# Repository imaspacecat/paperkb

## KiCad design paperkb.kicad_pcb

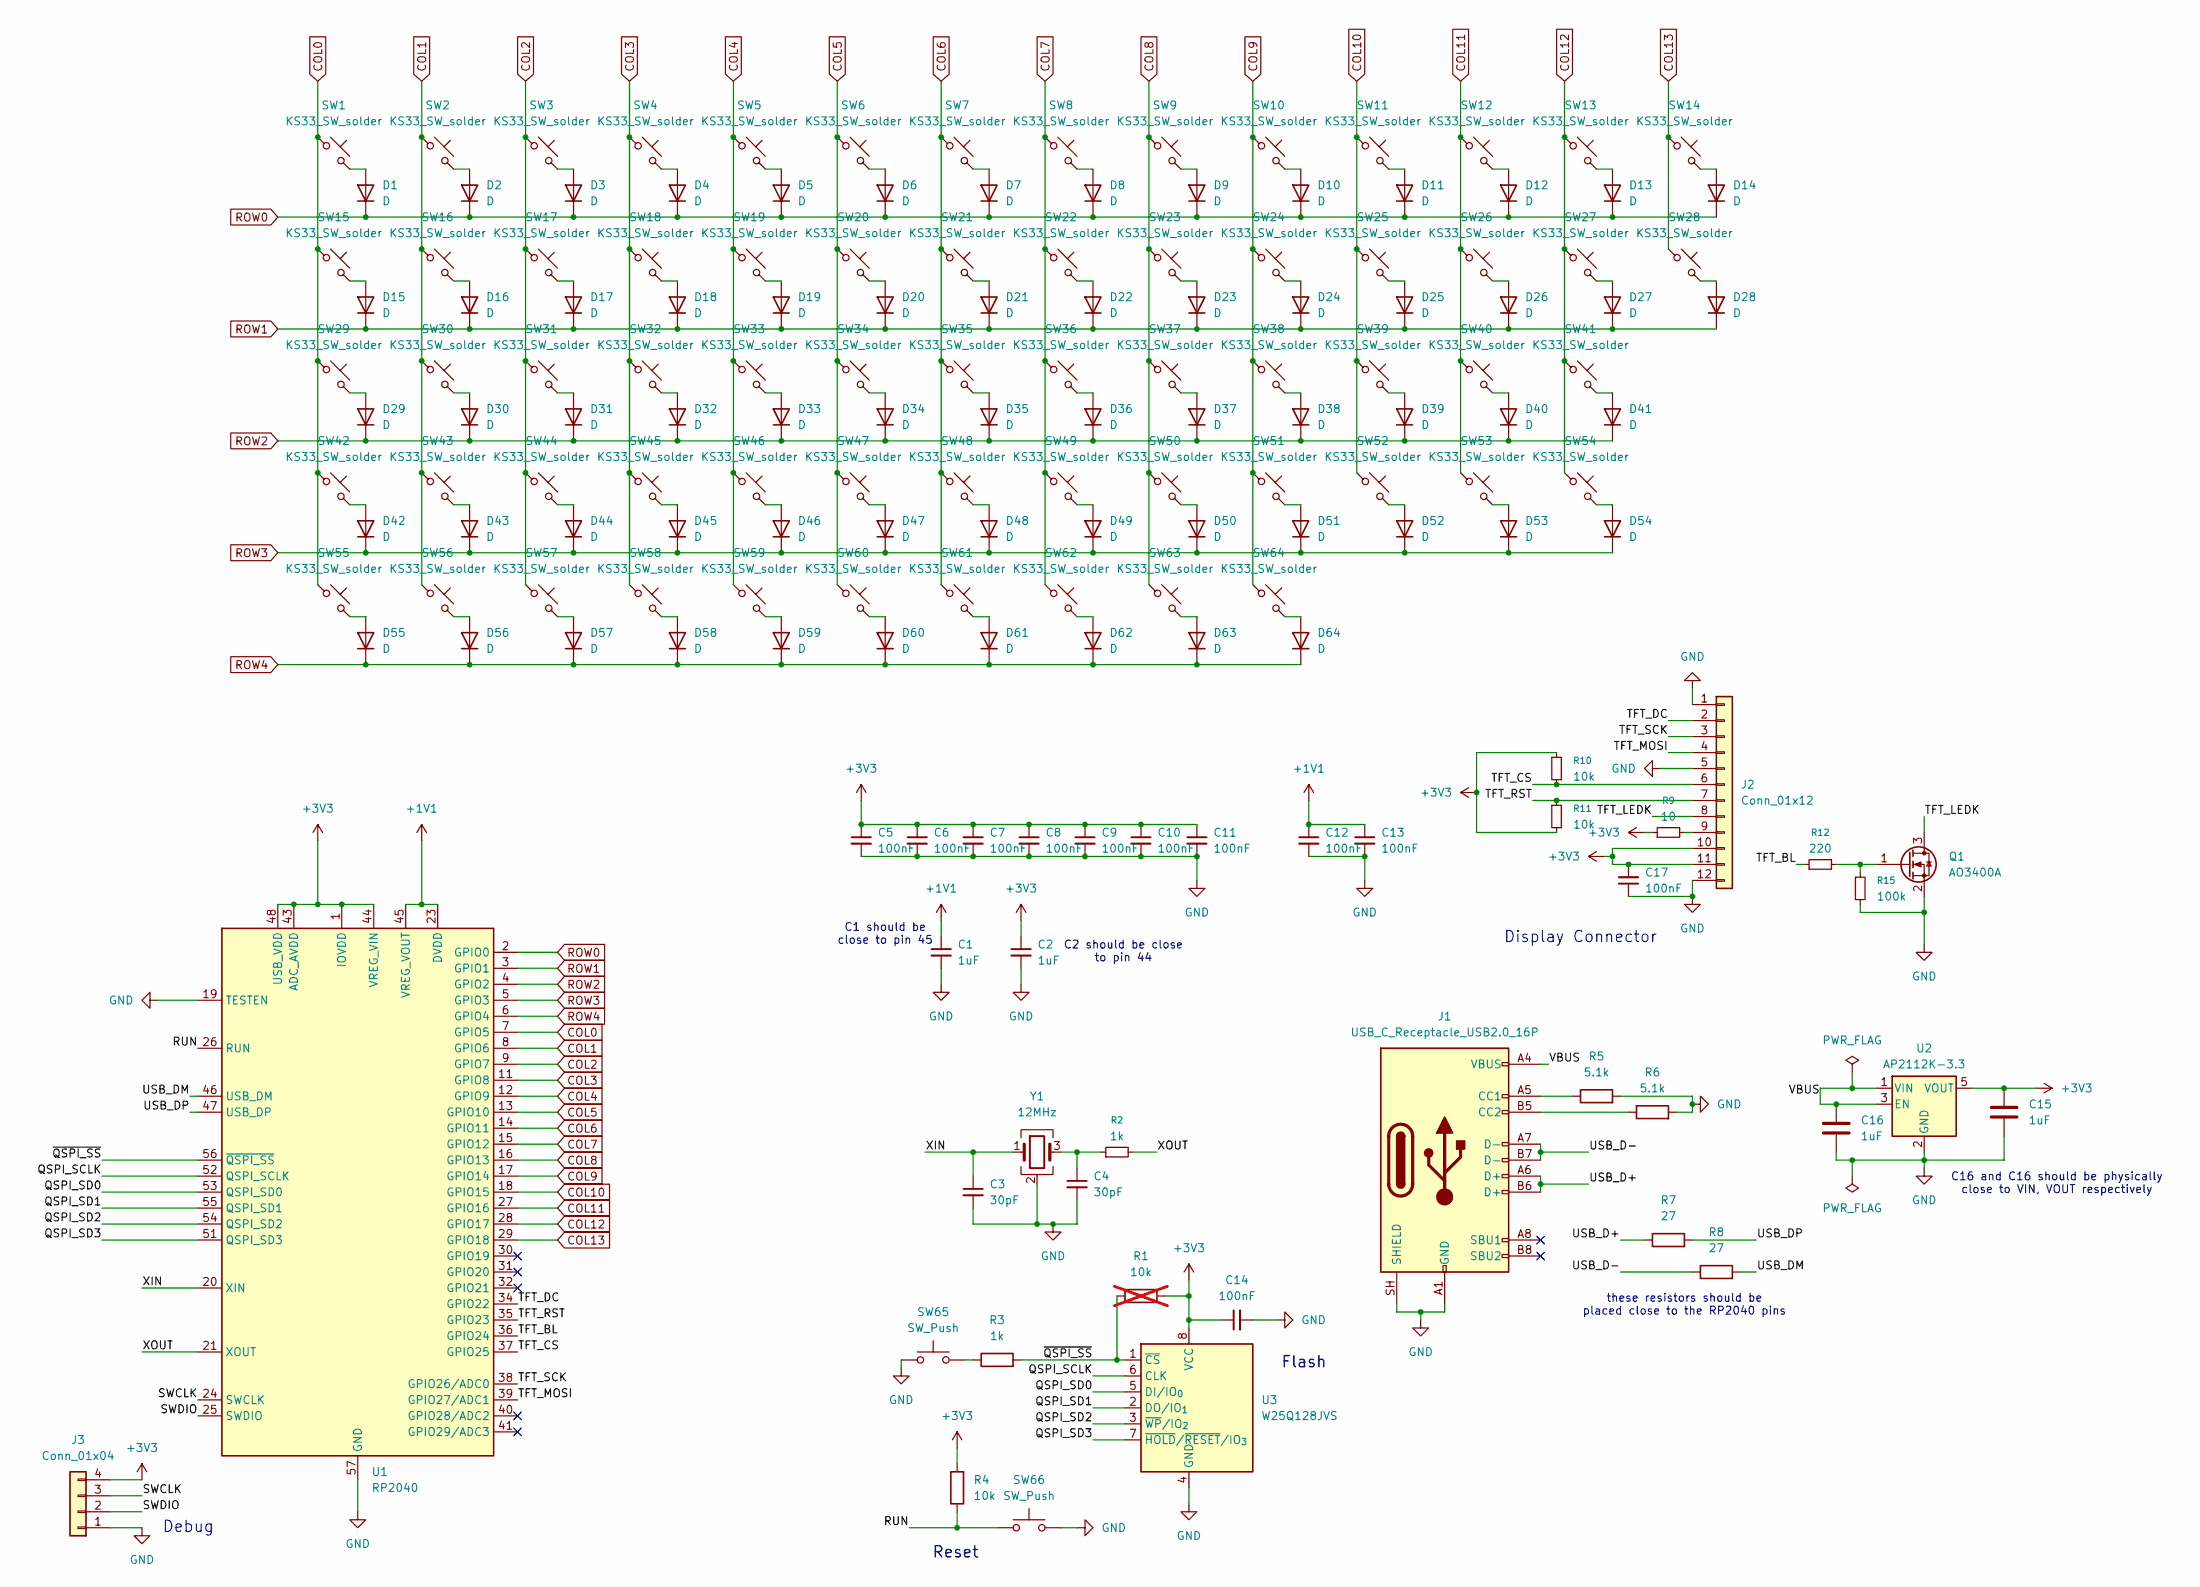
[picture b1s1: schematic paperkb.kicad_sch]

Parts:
C1, C2, C15, C16: 1uF; C_0603_1608Metric
C3, C4: 30pF; C_0603_1608Metric
C5, C6, C7, C8, C9, C10, C11, C12, C13, C14, C17: 100nF; C_0603_1608Metric
D1, D2, D3, D4, D5, D6, D7, D8, D9, D10, D11, D12, D13, D14, D15, D16, D17, D18, D19, D20, D21, D22, D23, D24, D25, D26, D27, D28, D29, D30, D31, D32, D33, D34, D35, D36, D37, D38, D39, D40, D41, D42, D43, D44, D45, D46, D47, D48, D49, D50, D51, D52, D53, D54, D55, D56, D57, D58, D59, D60, D61, D62, D63, D64: D; D_SOD-123
J1: USB_C_Receptacle_USB2.0_16P; USB_C_Receptacle_HRO_TYPE-C-31-M-12
J2: Conn_01x12; FPC-SMD_AFC01-S12FCA-00
J3: Conn_01x04; PinHeader_1x04_P2.54mm_Vertical
Q1: AO3400A; SOT-23
R1: 10k; R_0603_1608Metric; not fitted
R2, R3: 1k; R_0603_1608Metric
R4, R10, R11: 10k; R_0603_1608Metric
R5, R6: 5.1k; R_0603_1608Metric
R7, R8: 27; R_0603_1608Metric
R9: 10; R_0603_1608Metric
R12: 220; R_0603_1608Metric
R15: 100k; R_0603_1608Metric
SW1, SW2, SW3, SW4, SW5, SW6, SW7, SW8, SW9, SW10, SW11, SW12, SW13, SW14, SW15, SW16, SW17, SW18, SW19, SW20, SW21, SW22, SW23, SW24, SW25, SW26, SW27, SW28, SW29, SW30, SW31, SW32, SW33, SW34, SW35, SW36, SW37, SW38, SW39, SW40, SW41, SW42, SW43, SW44, SW45, SW46, SW47, SW48, SW49, SW50, SW51, SW52, SW53, SW54, SW55, SW56, SW57, SW58, SW59, SW60, SW61, SW62, SW63, SW64: KS33_SW_solder; SW_KS33_1u
SW65, SW66: SW_Push; SW_Push_1P1T_XKB_TS-1187A
U1: RP2040; QFN-56-1EP_7x7mm_P0.4mm_EP3.2x3.2mm
U2: AP2112K-3.3; SOT-23-5
U3: W25Q128JVS; SOIC-8_5.3x5.3mm_P1.27mm
Y1: 12MHz; Crystal_SMD_3225-4Pin_3.2x2.5mm

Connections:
+1V1: C1.1, C12.1, C13.1, U1.23 (DVDD), U1.45 (VREG_VOUT), U1.50 (DVDD)
+3V3: C2.1, C5.1, C6.1, C7.1, C8.1, C9.1, C10.1, C11.1, C14.1, C15.2, C17.2, J2.10, J2.11, J3.4, R1.2, R4.2, R9.1, R10.1, R11.2, U1.1 (IOVDD), U1.10 (IOVDD), U1.22 (IOVDD), U1.33 (IOVDD), U1.42 (IOVDD), U1.43 (ADC_AVDD), U1.44 (VREG_VIN), U1.48 (USB_VDD), U1.49 (IOVDD), U2.5 (VOUT), U3.8 (VCC)
/QSPI_SCLK: U1.52 (QSPI_SCLK), U3.6 (CLK)
/QSPI_SD0: U1.53 (QSPI_SD0), U3.5 (DI/IO_{0})
/QSPI_SD1: U1.55 (QSPI_SD1), U3.2 (DO/IO_{1})
/QSPI_SD2: U1.54 (QSPI_SD2), U3.3 (~WP/IO_{2})
/QSPI_SD3: U1.51 (QSPI_SD3), U3.7 (~HOLD/~RESET/IO_{3})
/RUN: R4.1, SW66.1, U1.26 (RUN)
/SWCLK: J3.3, U1.24 (SWCLK)
/SWDIO: J3.2, U1.25 (SWDIO)
/TFT_BL: R12.1, U1.36 (GPIO24)
/TFT_CS: J2.6, R10.2, U1.37 (GPIO25)
/TFT_DC: J2.2, U1.34 (GPIO22)
/TFT_LEDK: J2.8, Q1.3 (D)
/TFT_MOSI: J2.4, U1.39 (GPIO27/ADC1)
/TFT_RST: J2.7, R11.1, U1.35 (GPIO23)
/TFT_SCK: J2.3, U1.38 (GPIO26/ADC0)
/USB_D+: J1.A6 (D+), J1.B6 (D+), R7.1
/USB_D-: J1.A7 (D-), J1.B7 (D-), R8.1
/USB_DM: R8.2, U1.46 (USB_DM)
/USB_DP: R7.2, U1.47 (USB_DP)
/VBUS: C16.1, J1.A4 (VBUS), J1.A9 (VBUS), J1.B4 (VBUS), J1.B9 (VBUS), U2.1 (VIN), U2.3 (EN)
/XIN: C3.1, U1.20 (XIN), Y1.1
/XOUT: R2.2, U1.21 (XOUT)
/~QSPI_SS: R1.1, R3.2, U1.56 (~QSPI_SS), U3.1 (~CS)
COL0: SW1.1, SW15.1, SW29.1, SW42.1, SW55.1, U1.7 (GPIO5)
COL1: SW2.1, SW16.1, SW30.1, SW43.1, SW56.1, U1.8 (GPIO6)
COL2: SW3.1, SW17.1, SW31.1, SW44.1, SW57.1, U1.9 (GPIO7)
COL3: SW4.1, SW18.1, SW32.1, SW45.1, SW58.1, U1.11 (GPIO8)
COL4: SW5.1, SW19.1, SW33.1, SW46.1, SW59.1, U1.12 (GPIO9)
COL5: SW6.1, SW20.1, SW34.1, SW47.1, SW60.1, U1.13 (GPIO10)
COL6: SW7.1, SW21.1, SW35.1, SW48.1, SW61.1, U1.14 (GPIO11)
COL7: SW8.1, SW22.1, SW36.1, SW49.1, SW62.1, U1.15 (GPIO12)
COL8: SW9.1, SW23.1, SW37.1, SW50.1, SW63.1, U1.16 (GPIO13)
COL9: SW10.1, SW24.1, SW38.1, SW51.1, SW64.1, U1.17 (GPIO14)
COL10: SW11.1, SW25.1, SW39.1, SW52.1, U1.18 (GPIO15)
COL11: SW12.1, SW26.1, SW40.1, SW53.1, U1.27 (GPIO16)
COL12: SW13.1, SW27.1, SW41.1, SW54.1, U1.28 (GPIO17)
COL13: SW14.1, SW28.1, U1.29 (GPIO18)
GND: C1.2, C2.2, C3.2, C4.2, C5.2, C6.2, C7.2, C8.2, C9.2, C10.2, C11.2, C12.2, C13.2, C14.2, C15.1, C16.2, C17.1, J1.A1 (GND), J1.A12 (GND), J1.B1 (GND), J1.B12 (GND), J1.SH (SHIELD), J2.1, J2.5, J2.12, J3.1, Q1.2 (S), R5.2, R6.2, R15.2, SW65.1, SW66.2, U1.19 (TESTEN), U1.57 (GND), U2.2 (GND), U3.4 (GND), Y1.2 (G), Y1.4 (G)
unnamed: C4.1, R2.1, Y1.3
unnamed: D1.2 (A), SW1.2
unnamed: D2.2 (A), SW2.2
unnamed: D3.2 (A), SW3.2
unnamed: D4.2 (A), SW4.2
unnamed: D5.2 (A), SW5.2
unnamed: D6.2 (A), SW6.2
unnamed: D7.2 (A), SW7.2
unnamed: D8.2 (A), SW8.2
unnamed: D9.2 (A), SW9.2
unnamed: D10.2 (A), SW10.2
unnamed: D11.2 (A), SW11.2
unnamed: D12.2 (A), SW12.2
unnamed: D13.2 (A), SW13.2
unnamed: D14.2 (A), SW14.2
unnamed: D15.2 (A), SW15.2
unnamed: D16.2 (A), SW16.2
unnamed: D17.2 (A), SW17.2
unnamed: D18.2 (A), SW18.2
unnamed: D19.2 (A), SW19.2
unnamed: D20.2 (A), SW20.2
unnamed: D21.2 (A), SW21.2
unnamed: D22.2 (A), SW22.2
unnamed: D23.2 (A), SW23.2
unnamed: D24.2 (A), SW24.2
unnamed: D25.2 (A), SW25.2
unnamed: D26.2 (A), SW26.2
unnamed: D27.2 (A), SW27.2
unnamed: D28.2 (A), SW28.2
unnamed: D29.2 (A), SW29.2
unnamed: D30.2 (A), SW30.2
unnamed: D31.2 (A), SW31.2
unnamed: D32.2 (A), SW32.2
unnamed: D33.2 (A), SW33.2
unnamed: D34.2 (A), SW34.2
unnamed: D35.2 (A), SW35.2
unnamed: D36.2 (A), SW36.2
unnamed: D37.2 (A), SW37.2
unnamed: D38.2 (A), SW38.2
unnamed: D39.2 (A), SW39.2
unnamed: D40.2 (A), SW40.2
unnamed: D41.2 (A), SW41.2
unnamed: D42.2 (A), SW42.2
unnamed: D43.2 (A), SW43.2
unnamed: D44.2 (A), SW44.2
unnamed: D45.2 (A), SW45.2
unnamed: D46.2 (A), SW46.2
unnamed: D47.2 (A), SW47.2
unnamed: D48.2 (A), SW48.2
unnamed: D49.2 (A), SW49.2
unnamed: D50.2 (A), SW50.2
unnamed: D51.2 (A), SW51.2
unnamed: D52.2 (A), SW52.2
unnamed: D53.2 (A), SW53.2
unnamed: D54.2 (A), SW54.2
unnamed: D55.2 (A), SW55.2
unnamed: D56.2 (A), SW56.2
unnamed: D57.2 (A), SW57.2
unnamed: D58.2 (A), SW58.2
unnamed: D59.2 (A), SW59.2
unnamed: D60.2 (A), SW60.2
unnamed: D61.2 (A), SW61.2
unnamed: D62.2 (A), SW62.2
unnamed: D63.2 (A), SW63.2
unnamed: D64.2 (A), SW64.2
unnamed: J1.A5 (CC1), R5.1
unnamed: J1.B5 (CC2), R6.1
unnamed: J2.9, R9.2
unnamed: Q1.1 (G), R12.2, R15.1
unnamed: R3.1, SW65.2
ROW0: D1.1 (K), D2.1 (K), D3.1 (K), D4.1 (K), D5.1 (K), D6.1 (K), D7.1 (K), D8.1 (K), D9.1 (K), D10.1 (K), D11.1 (K), D12.1 (K), D13.1 (K), D14.1 (K), U1.2 (GPIO0)
ROW1: D15.1 (K), D16.1 (K), D17.1 (K), D18.1 (K), D19.1 (K), D20.1 (K), D21.1 (K), D22.1 (K), D23.1 (K), D24.1 (K), D25.1 (K), D26.1 (K), D27.1 (K), D28.1 (K), U1.3 (GPIO1)
ROW2: D29.1 (K), D30.1 (K), D31.1 (K), D32.1 (K), D33.1 (K), D34.1 (K), D35.1 (K), D36.1 (K), D37.1 (K), D38.1 (K), D39.1 (K), D40.1 (K), D41.1 (K), U1.4 (GPIO2)
ROW3: D42.1 (K), D43.1 (K), D44.1 (K), D45.1 (K), D46.1 (K), D47.1 (K), D48.1 (K), D49.1 (K), D50.1 (K), D51.1 (K), D52.1 (K), D53.1 (K), D54.1 (K), U1.5 (GPIO3)
ROW4: D55.1 (K), D56.1 (K), D57.1 (K), D58.1 (K), D59.1 (K), D60.1 (K), D61.1 (K), D62.1 (K), D63.1 (K), D64.1 (K), U1.6 (GPIO4)

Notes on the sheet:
Flash
Display Connector
Debug
C2 should be close to pin 44
Reset
C16 and C16 should be physically close to VIN, VOUT respectively
these resistors should be placed close to the RP2040 pins
C1 should be close to pin 45

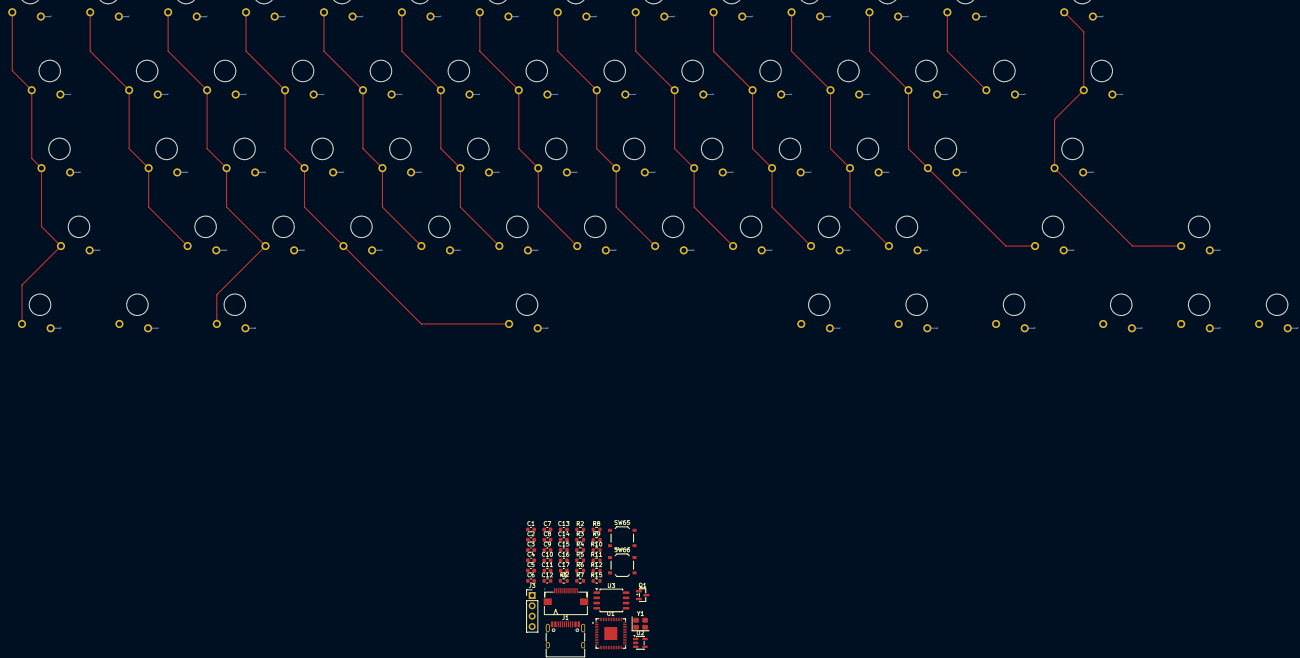
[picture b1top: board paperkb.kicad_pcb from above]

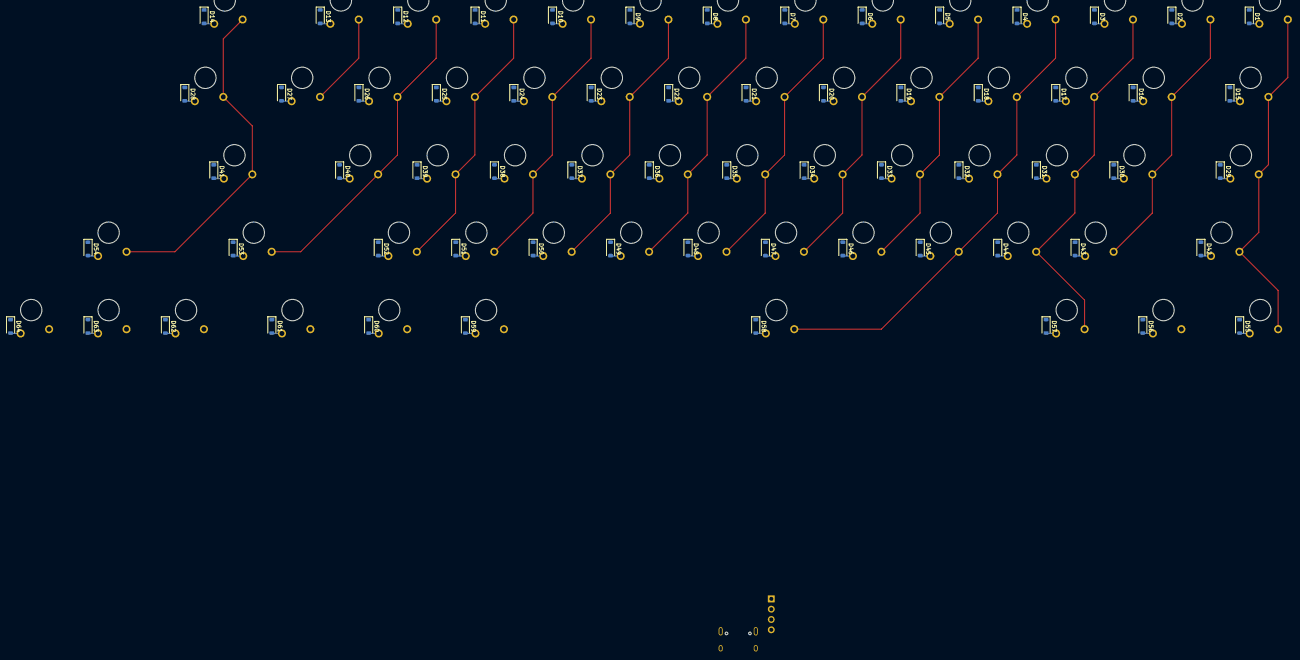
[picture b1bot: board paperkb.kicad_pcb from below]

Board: 2 copper layers, 168 parts (64 on the bottom side), 115 nets.
